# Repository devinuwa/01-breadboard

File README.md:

# 01-breadboard

Power supply for a breadboard, with a 5 V rail and a 3.3 V rail.

If you want to make one of these for yourself, you can use this design as it is, or alter it and make it better.
The KiCad project files are in this repository, so you can open the design, change it and send it to the board house of your choice.

## Images

Top side:

Bottom side:

## Design notes

- Power comes in through the barrel jack **J1**.
- **U1** and **U2** are the two voltage regulators (the board is marked 3.3 V and 5 V).
- **C1 to C4** are the input and output capacitors for the regulators.
- **D1** with **R1** is the power indicator LED.
- **J2** and **J3** are the 4-pin headers at the top edge. The row of holes along the edges lines up with a breadboard's power rails.
- Designed in [KiCad](https://www.kicad.org/). The design has no design-rule (DRC) violations.

## Project files

| File | What it is |
|---|---|
| `01-breadboard.kicad_pro` | KiCad project |
| `01-breadboard.kicad_sch` | Schematic |
| `01-breadboard.kicad_pcb` | PCB layout |
| `images/` | Renders of the board used in this README |

## License

Copyright (C) 2019 John Winans
Modifications Copyright (C) 2026 Muhammad Inuwa Muhammad

This documentation describes Open Hardware and is licensed under the CERN OHL v. 1.2.
You may redistribute and modify this documentation under the terms of the CERN OHL v.1.2.
(http://ohwr.org/cernohl). This documentation is distributed WITHOUT ANY EXPRESS OR
IMPLIED WARRANTY, INCLUDING OF MERCHANTABILITY, SATISFACTORY QUALITY AND FITNESS FOR A
PARTICULAR PURPOSE. Please see the CERN OHL v.1.2 for applicable conditions.

If you choose to manufacture products based on this design, please notify the
modifier (see license section 4.2) via inuwamuhammad930@gmail.com

## Credits

This design is a modified version of the original work by John Winans:
https://github.com/johnwinans/2044-breadboard-power

## Author

Muhammad Inuwa Muhammad, inuwamuhammad930@gmail.com

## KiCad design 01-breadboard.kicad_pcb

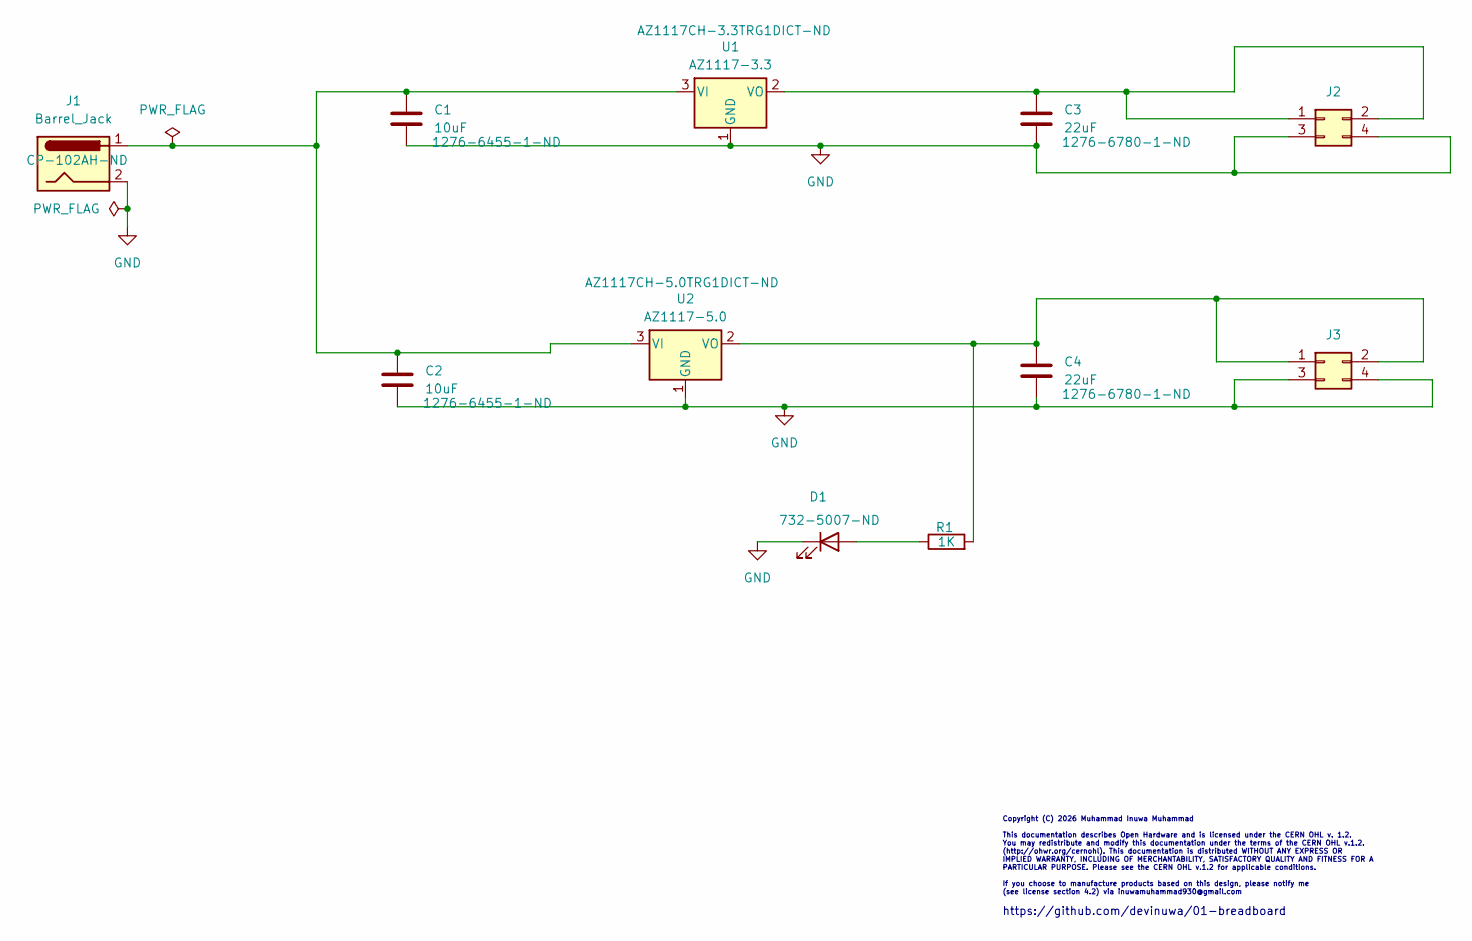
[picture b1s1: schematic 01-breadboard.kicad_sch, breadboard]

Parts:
C1, C2: 10uF; C_0805_2012Metric_Pad1.18x1.45mm_HandSolder; digikey 1276-6455-1-ND
C3, C4: 22uF; C_0805_2012Metric_Pad1.18x1.45mm_HandSolder; digikey 1276-6780-1-ND
D1: LED; LED_D3.0mm; Digikey 732-5007-ND
J1: Barrel_Jack; BarrelJack_CUI_PJ-102AH_Horizontal; Digikey CP-102AH-ND
J2, J3: Conn_02x02_Odd_Even; PinHeader_2x02_P2.54mm_Vertical
R1: 1K; R_0805_2012Metric_Pad1.20x1.40mm_HandSolder
U1: AZ1117-3.3; SOT-223-3_TabPin2; Digikey AZ1117CH-3.3TRG1DICT-ND
U2: AZ1117-5.0; SOT-223-3_TabPin2; Digikey AZ1117CH-5.0TRG1DICT-ND

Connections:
GND: C1.2, C2.2, C3.2, C4.2, D1.1 (K), J1.2, J2.3, J2.4, J3.3, J3.4, U1.1 (GND), U2.1 (GND)
unnamed: D1.2 (A), R1.1
unnamed: C3.1, J2.1, J2.2, U1.2 (VO)
unnamed: C4.1, J3.1, J3.2, R1.2, U2.2 (VO)
unnamed: C1.1, C2.1, J1.1, U1.3 (VI), U2.3 (VI)

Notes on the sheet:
Copyright (C) 2026 Muhammad Inuwa Muhammad This documentation describes Open Hardware and is licensed under the CERN OHL v. 1.2. You may redistribute and modify this documentation under the terms of the CERN OHL v.1.2. (http://ohwr.org/cernohl). This documentation is distributed WITHOUT ANY EXPRESS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
https://github.com/devinuwa/01-breadboard

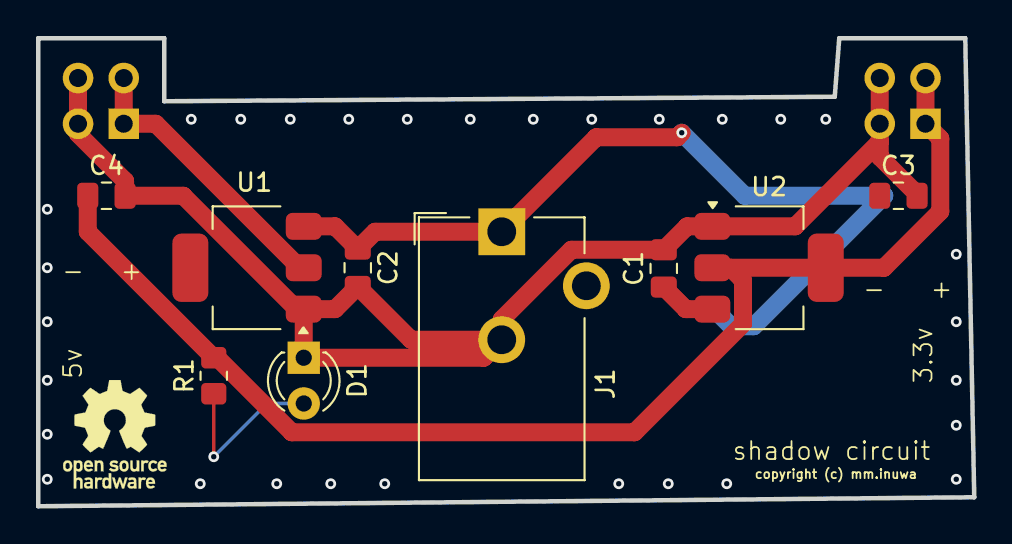
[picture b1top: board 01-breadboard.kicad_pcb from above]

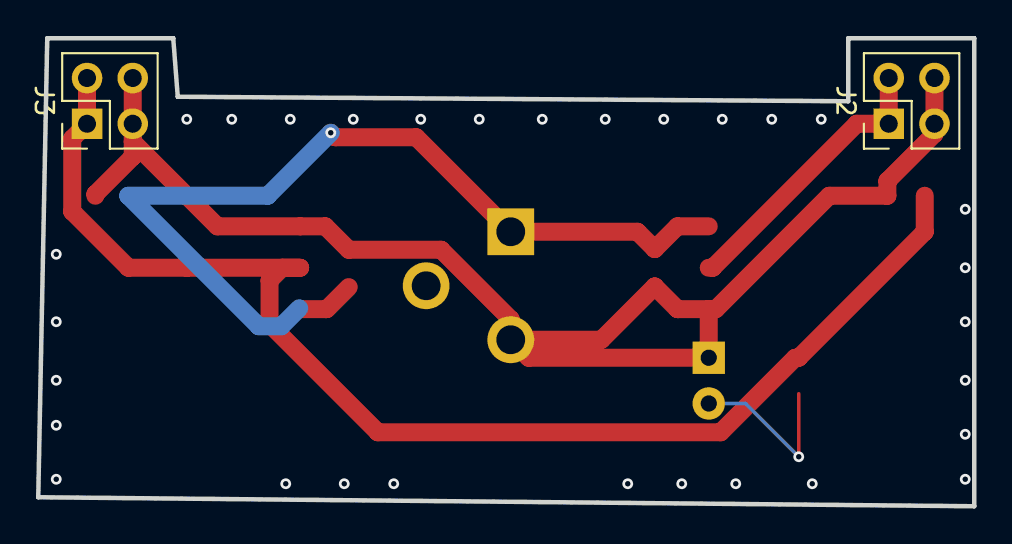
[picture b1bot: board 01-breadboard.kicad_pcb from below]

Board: 2 copper layers, 52.0 x 26.0 mm, 11 parts (2 on the bottom side), 5 nets.

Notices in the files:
01-breadboard.kicad_pcb:
copyright (c) mm.inuwa
